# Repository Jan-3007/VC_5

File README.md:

# Project VC 5

Note: This project is still under development.

finished parts:
- Firmware
- PC app (basic functionality)
- schematic

under development:
- 3D model for the case
- PC app (features for better useability)

future:
- support for Linux

## General description
The aim of this project is to create an external device, which allows the user to adjust the volume of various programs on a host PC. 

## Hardware
A number of rotaries are available as input (number set to 5 within the config file of this project) and LED's and displays to show any kind of status.
The schematic for the device can be found at _Harware/schematic_.
Note: Soldering Pads in the schematic might be 0.1 mm thick, still working on a solution.

## Software
The software consists of two parts.

### 1. Firmware
The firmware is written for the Raspberry Pi RP2040. It communicates via USB with the host PC. The firmware only transmits data from the rotaries to the host PC and executes commands from the host PC. These commands can for example set the color of the LED and change the content shown on the displays.

### 2. PC application
The PC application (only Windows) acts as the executing intelligence. It takes the data from the rotaries and processes it. The volume of five different audio channels is controlled. The application can also send commands to the device to e.g. set the LED color or write information on the displays.

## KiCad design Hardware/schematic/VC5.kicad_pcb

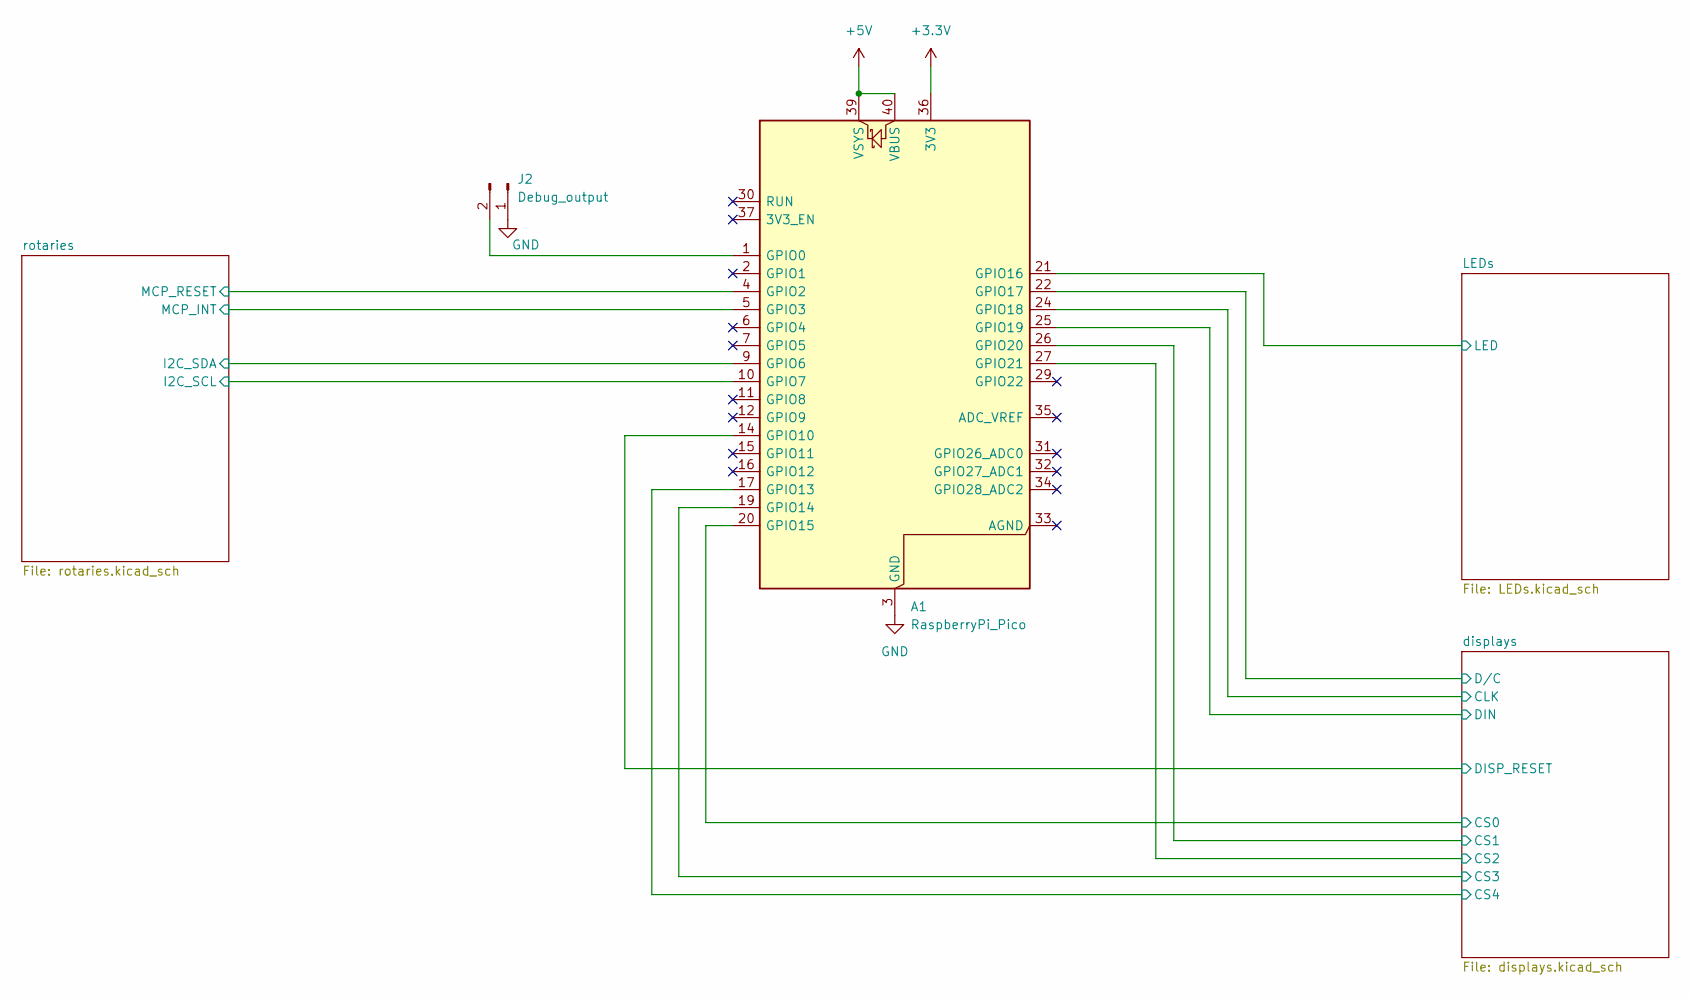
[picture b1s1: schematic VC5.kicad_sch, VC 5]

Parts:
A1: RaspberryPi_Pico; RaspberryPi_Pico_Common_THT_custom
J2: Debug_output; PinHeader_1x02_P2.54mm_Vertical

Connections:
+3.3V: A1.36 (3V3); also elsewhere on the board
+5V: A1.39 (VSYS), A1.40 (VBUS); also elsewhere on the board
/LEDs/LED: A1.21 (GPIO16); also elsewhere on the board
/displays/CLK: A1.24 (GPIO18); also elsewhere on the board
/displays/CS0: A1.20 (GPIO15); also elsewhere on the board
/displays/CS1: A1.26 (GPIO20); also elsewhere on the board
/displays/CS2: A1.27 (GPIO21); also elsewhere on the board
/displays/CS3: A1.19 (GPIO14); also elsewhere on the board
/displays/CS4: A1.17 (GPIO13); also elsewhere on the board
/displays/DIN: A1.25 (GPIO19); also elsewhere on the board
/displays/DISP_RESET: A1.14 (GPIO10); also elsewhere on the board
/displays/D/C: A1.22 (GPIO17); also elsewhere on the board
/rotaries/I2C_SCL: A1.10 (GPIO7); also elsewhere on the board
/rotaries/I2C_SDA: A1.9 (GPIO6); also elsewhere on the board
/rotaries/MCP_INT: A1.5 (GPIO3); also elsewhere on the board
/rotaries/MCP_RESET: A1.4 (GPIO2); also elsewhere on the board
GND: A1.3 (GND), A1.8 (GND), A1.13 (GND), A1.18 (GND), A1.23 (GND), A1.28 (GND), A1.38 (GND), J2.1; also elsewhere on the board
unnamed: A1.1 (GPIO0), J2.2

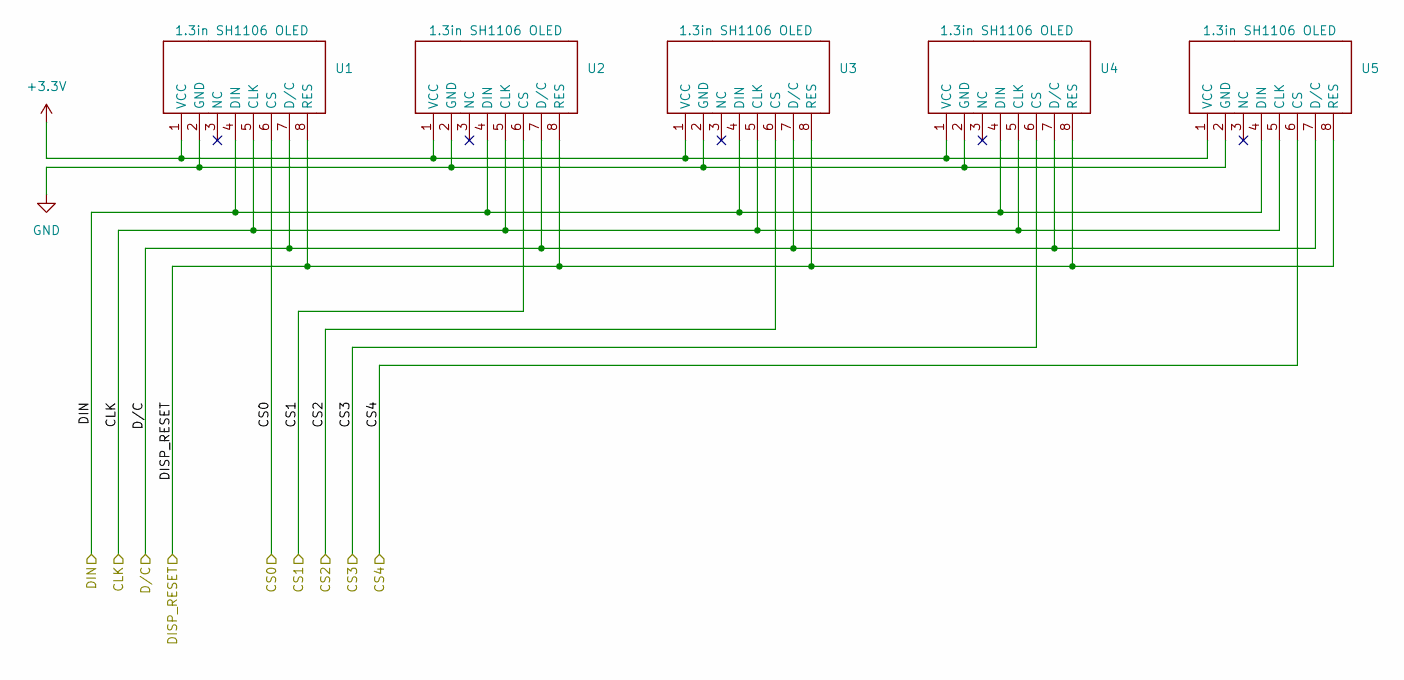
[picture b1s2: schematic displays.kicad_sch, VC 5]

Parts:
U1, U2, U3, U4, U5: 1.3in SH1106 OLED; PinHeader_1x08_P2.54mm_Vertical_Display

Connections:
+3.3V: U1.1 (VCC), U2.1 (VCC), U3.1 (VCC), U4.1 (VCC), U5.1 (VCC); also elsewhere on the board
/displays/CLK: U1.5 (CLK), U2.5 (CLK), U3.5 (CLK), U4.5 (CLK), U5.5 (CLK); also elsewhere on the board
/displays/CS0: U1.6 (CS); also elsewhere on the board
/displays/CS1: U2.6 (CS); also elsewhere on the board
/displays/CS2: U3.6 (CS); also elsewhere on the board
/displays/CS3: U4.6 (CS); also elsewhere on the board
/displays/CS4: U5.6 (CS); also elsewhere on the board
/displays/DIN: U1.4 (DIN), U2.4 (DIN), U3.4 (DIN), U4.4 (DIN), U5.4 (DIN); also elsewhere on the board
/displays/DISP_RESET: U1.8 (RES), U2.8 (RES), U3.8 (RES), U4.8 (RES), U5.8 (RES); also elsewhere on the board
/displays/D/C: U1.7 (D/C), U2.7 (D/C), U3.7 (D/C), U4.7 (D/C), U5.7 (D/C); also elsewhere on the board
GND: U1.2 (GND), U2.2 (GND), U3.2 (GND), U4.2 (GND), U5.2 (GND); also elsewhere on the board

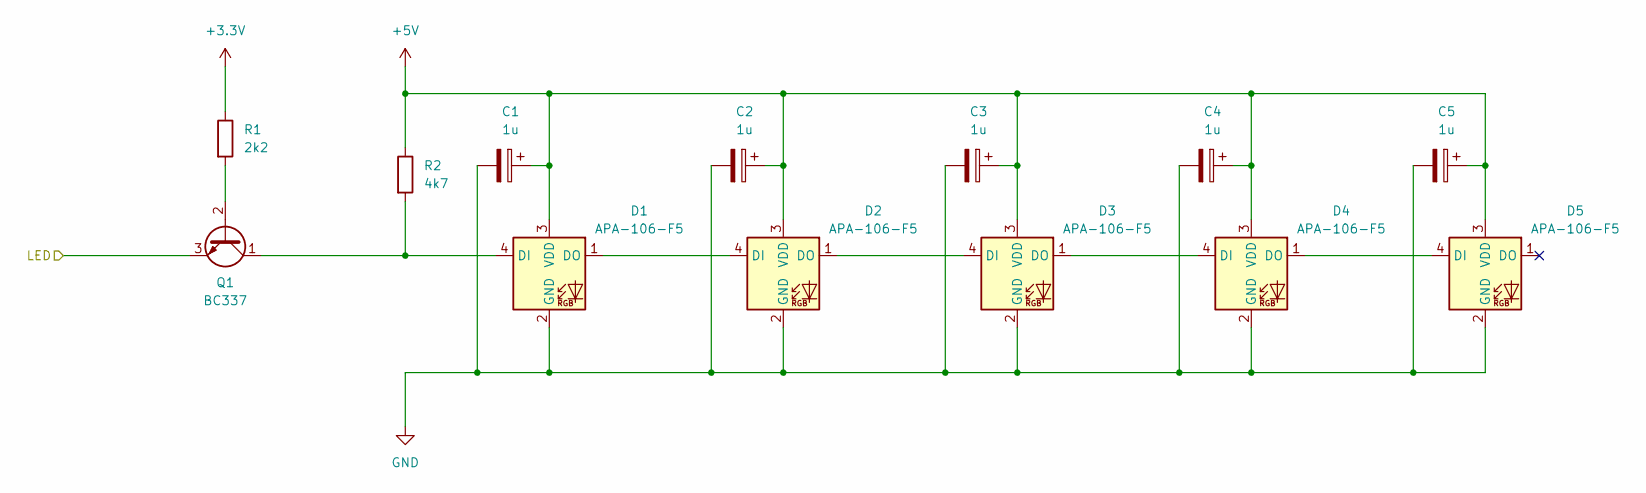
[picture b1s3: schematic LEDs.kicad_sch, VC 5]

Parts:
C1, C2, C3, C4, C5: 1u; CP_Radial_D5.0mm_P2.00mm
D1, D2, D3, D4, D5: APA-106-F5; LED_D5.0mm-4_RGB_Wide_Pins
Q1: BC337; TO-92_Inline
R1: 2k2; R_Axial_DIN0204_L3.6mm_D1.6mm_P7.62mm_Horizontal
R2: 4k7; R_Axial_DIN0204_L3.6mm_D1.6mm_P7.62mm_Horizontal

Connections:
+3.3V: R1.1; also elsewhere on the board
+5V: C1.1, C2.1, C3.1, C4.1, C5.1, D1.3 (VDD), D2.3 (VDD), D3.3 (VDD), D4.3 (VDD), D5.3 (VDD), R2.1; also elsewhere on the board
/LEDs/LED: Q1.3 (E); also elsewhere on the board
GND: C1.2, C2.2, C3.2, C4.2, C5.2, D1.2 (GND), D2.2 (GND), D3.2 (GND), D4.2 (GND), D5.2 (GND); also elsewhere on the board
unnamed: D1.4 (DI), Q1.1 (C), R2.2
unnamed: D1.1 (DO), D2.4 (DI)
unnamed: D2.1 (DO), D3.4 (DI)
unnamed: D3.1 (DO), D4.4 (DI)
unnamed: D4.1 (DO), D5.4 (DI)
unnamed: Q1.2 (B), R1.2

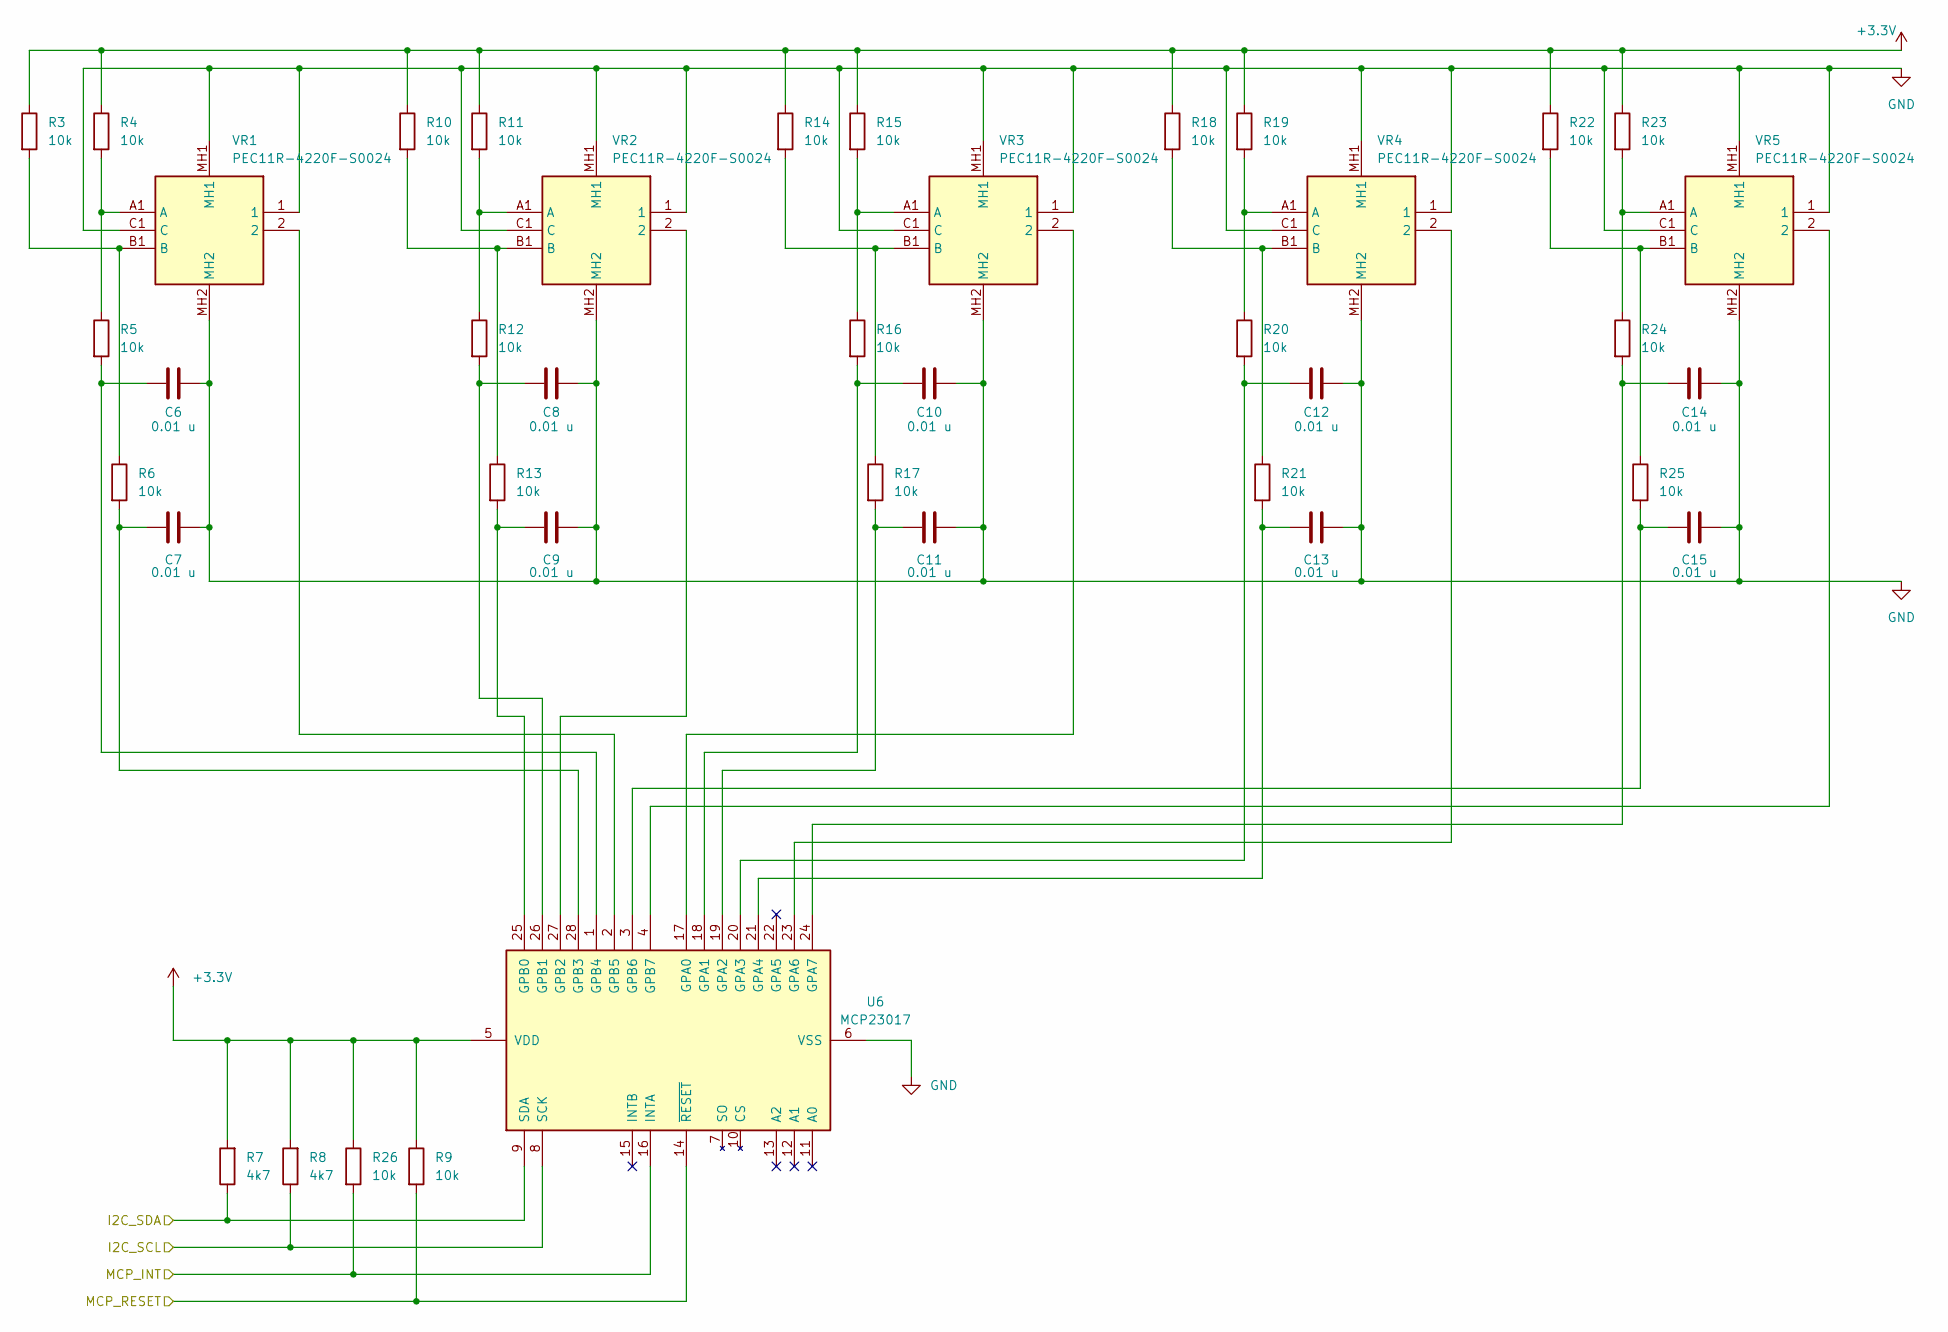
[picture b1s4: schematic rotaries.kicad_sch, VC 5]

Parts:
C6, C7, C8, C9, C10, C11, C12, C13, C14, C15: 0.01 u; C_Disc_D5.0mm_W2.5mm_P2.50mm
R3, R4, R5, R6, R9, R10, R11, R12, R13, R14, R15, R16, R17, R18, R19, R20, R21, R22, R23, R24, R25, R26: 10k; R_Axial_DIN0204_L3.6mm_D1.6mm_P7.62mm_Horizontal
R7, R8: 4k7; R_Axial_DIN0204_L3.6mm_D1.6mm_P7.62mm_Horizontal
U6: MCP23017; MCP23017_IO_expander
VR1, VR2, VR3, VR4, VR5: PEC11R-4220F-S0024; PEC11R4220FS0024; Manufacturer_Part_Number PEC11R-4220F-S0024; Mouser Part Number 652-PEC11R-4220F-S24

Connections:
+3.3V: R3.1, R4.1, R7.2, R8.2, R9.1, R10.1, R11.1, R14.1, R15.1, R18.1, R19.1, R22.1, R23.1, R26.1, U6.5 (VDD); also elsewhere on the board
/rotaries/I2C_SCL: R8.1, U6.8 (SCK); also elsewhere on the board
/rotaries/I2C_SDA: R7.1, U6.9 (SDA); also elsewhere on the board
/rotaries/MCP_INT: R26.2, U6.16 (INTA); also elsewhere on the board
/rotaries/MCP_RESET: R9.2, U6.14 (~RESET); also elsewhere on the board
GND: C6.2, C7.2, C8.2, C9.2, C10.2, C11.2, C12.2, C13.2, C14.2, C15.2, U6.6 (VSS), VR1.1, VR1.C1 (C), VR1.MH1, VR1.MH2, VR2.1, VR2.C1 (C), VR2.MH1, VR2.MH2, VR3.1, VR3.C1 (C), VR3.MH1, VR3.MH2, VR4.1, VR4.C1 (C), VR4.MH1, VR4.MH2, VR5.1, VR5.C1 (C), VR5.MH1, VR5.MH2; also elsewhere on the board
unnamed: U6.17 (GPA0), VR3.2
unnamed: C10.1, R16.2, U6.18 (GPA1)
unnamed: C11.1, R17.2, U6.19 (GPA2)
unnamed: C12.1, R20.2, U6.20 (GPA3)
unnamed: C13.1, R21.2, U6.21 (GPA4)
unnamed: U6.23 (GPA6), VR4.2
unnamed: C14.1, R24.2, U6.24 (GPA7)
unnamed: C9.1, R13.2, U6.25 (GPB0)
unnamed: C8.1, R12.2, U6.26 (GPB1)
unnamed: U6.27 (GPB2), VR2.2
unnamed: C7.1, R6.2, U6.28 (GPB3)
unnamed: C6.1, R5.2, U6.1 (GPB4)
unnamed: U6.2 (GPB5), VR1.2
unnamed: C15.1, R25.2, U6.3 (GPB6)
unnamed: U6.4 (GPB7), VR5.2
unnamed: R4.2, R5.1, VR1.A1 (A)
unnamed: R3.2, R6.1, VR1.B1 (B)
unnamed: R11.2, R12.1, VR2.A1 (A)
unnamed: R10.2, R13.1, VR2.B1 (B)
unnamed: R15.2, R16.1, VR3.A1 (A)
unnamed: R14.2, R17.1, VR3.B1 (B)
unnamed: R19.2, R20.1, VR4.A1 (A)
unnamed: R18.2, R21.1, VR4.B1 (B)
unnamed: R23.2, R24.1, VR5.A1 (A)
unnamed: R22.2, R25.1, VR5.B1 (B)

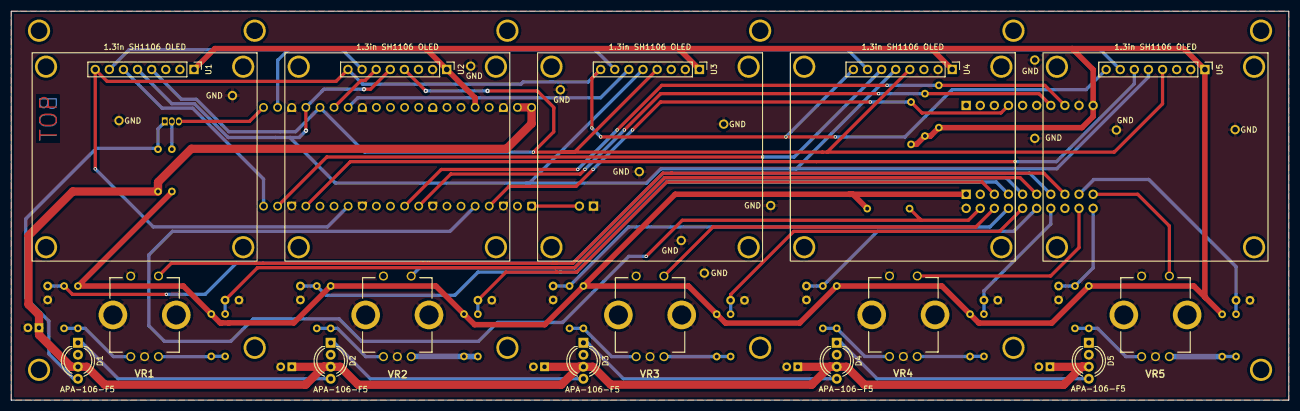
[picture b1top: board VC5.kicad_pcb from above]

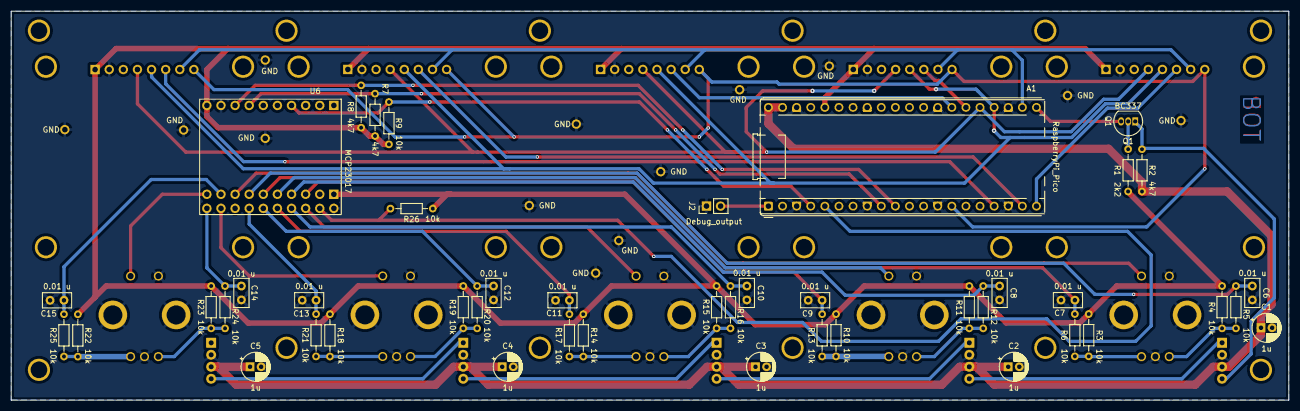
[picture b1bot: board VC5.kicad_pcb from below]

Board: 2 copper layers, 230.0 x 70.0 mm, 60 parts (45 on the bottom side), 49 nets.

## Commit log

2025-03-12 added initial files of base project 'Project_VC_5'
2025-03-12 added initial WinApp files from base project 'Project_VC_5'
2025-03-21 additional firmware files
2025-03-21 added schematic files
2025-03-21 fixed missing schematic symbols
2025-04-20 fixed an error in the filters for the rotaries
2025-04-29 updated footprints and corresponding 3D models
2025-04-30 added pcb parameters, positioned LEDs
2025-05-05 trace routing completed
2025-05-06 added final trace adjustments and mounting holes
2025-05-06 first final version
2025-05-08 updated PCB layout
2025-05-08 fixed missing interrupt line
2025-05-12 final version of the PCB
2025-05-12 reorganized schematic files
2025-05-12 removed KiCAD backups
2025-09-15 fixed mistake in the schematic
2025-09-15 updated Firmware config file
2025-09-16 adjustments to the PCB layout after schematic change
2025-09-20 added README and License
2025-09-20 updated 3D model
2025-09-21 added mounting for PCB to the front plate
